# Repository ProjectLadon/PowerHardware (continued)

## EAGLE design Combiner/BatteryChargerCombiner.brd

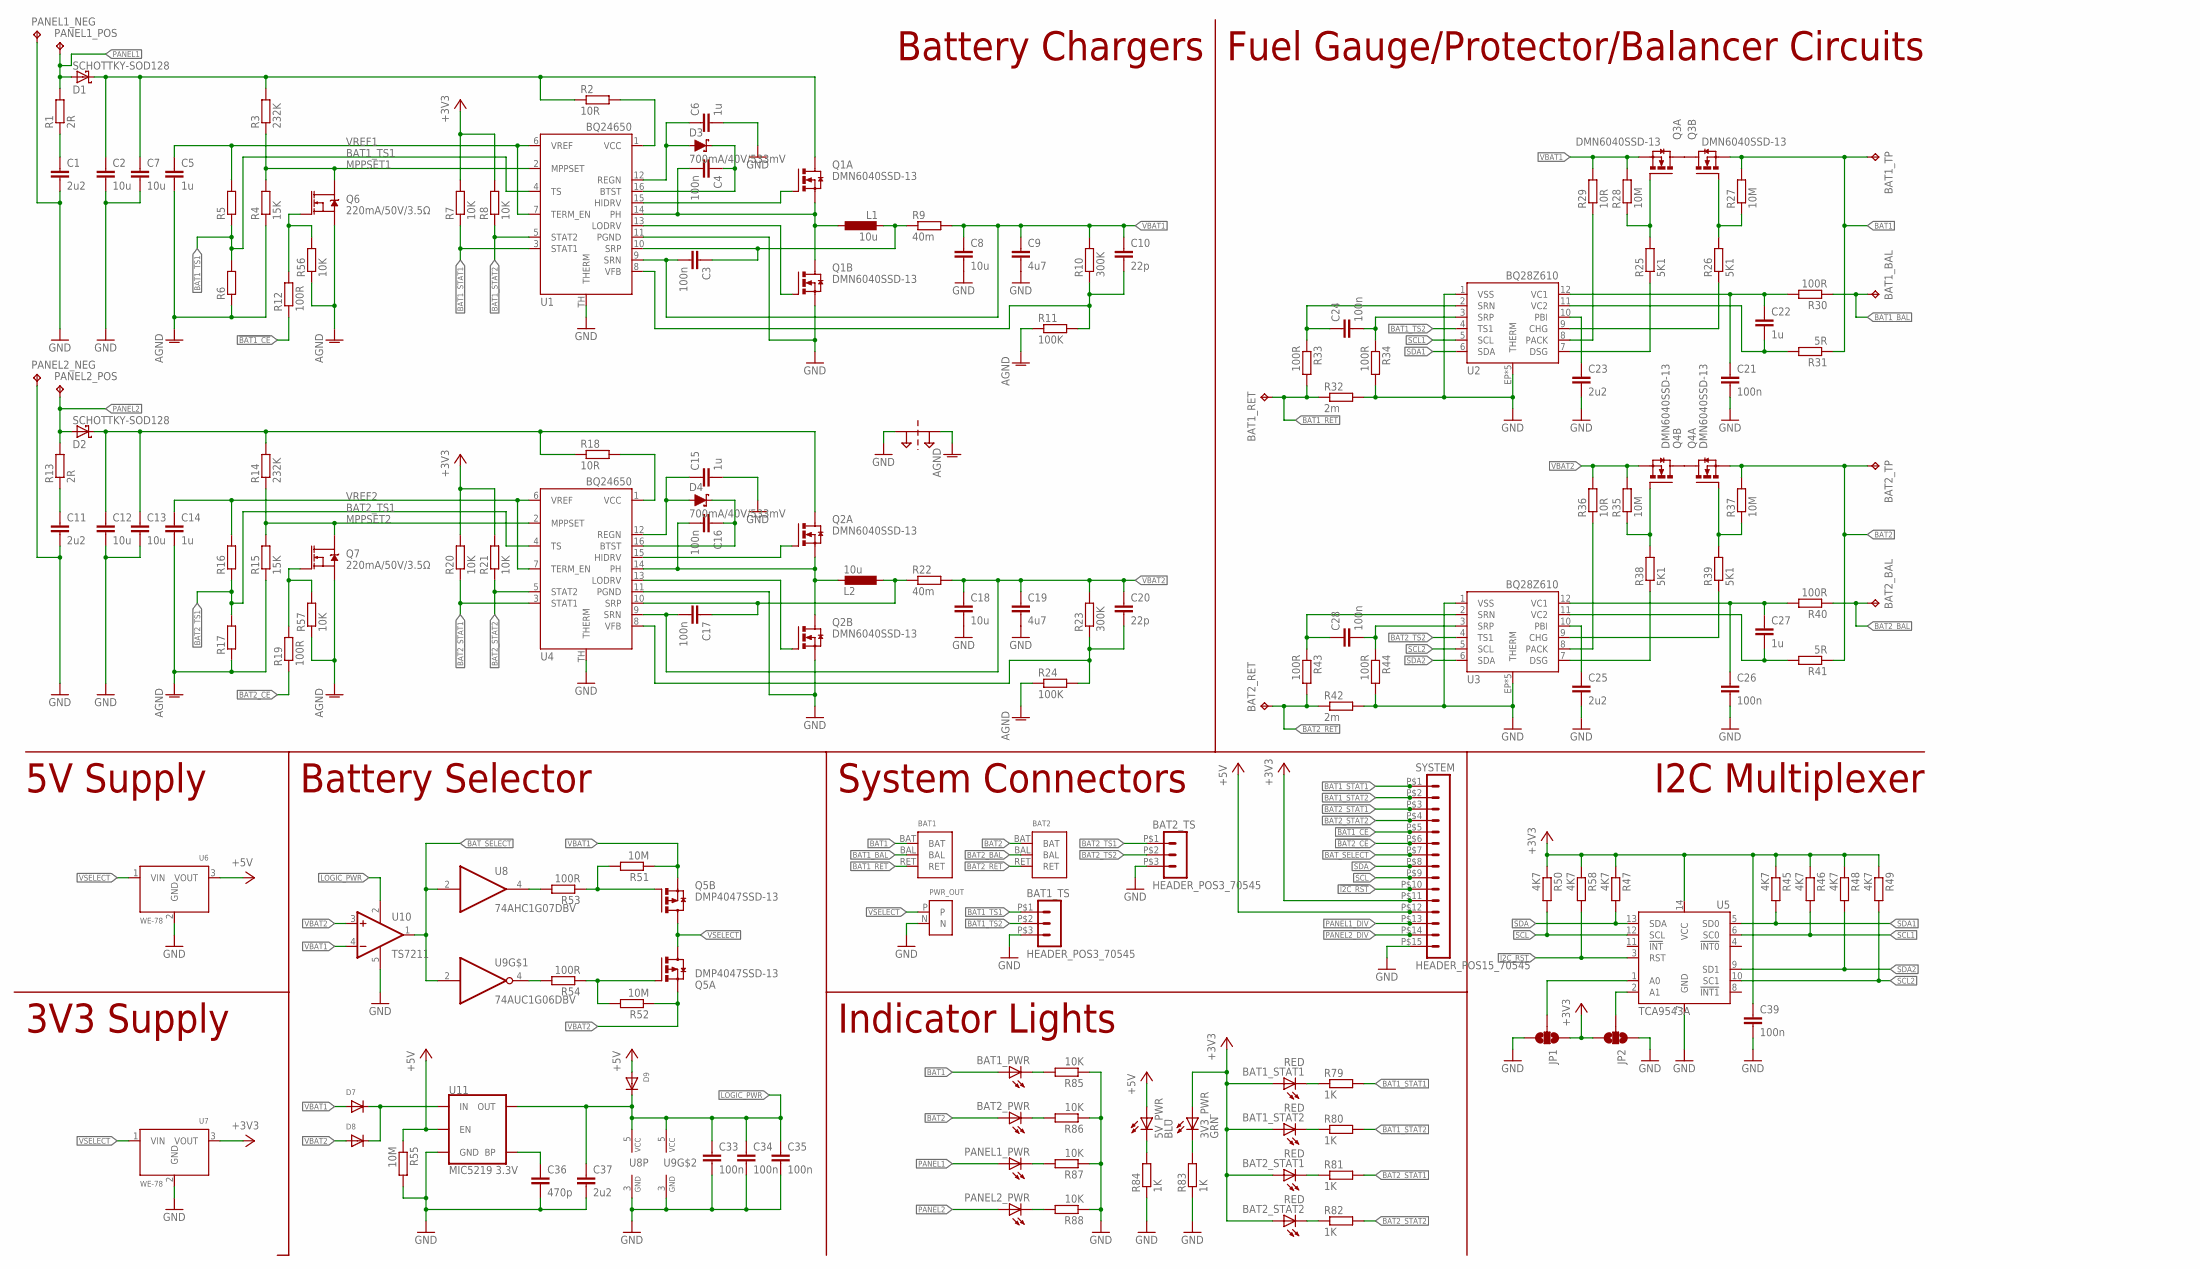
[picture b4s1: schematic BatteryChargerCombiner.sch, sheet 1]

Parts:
3V3_PWR: GRN; CHIP-LED0603
5V_PWR: BLU; CHIP-LED0603
BAT1, BAT2: 2S-BATTERYSMD; JST-XH3-SMD
BAT1_BAL, BAT1_RET, BAT1_TP, BAT2_BAL, BAT2_RET, BAT2_TP: TPPAD1-13Y; P1-13Y
BAT1_PWR, BAT2_PWR: LEDCHIP-LED0603; CHIP-LED0603
BAT1_STAT1, BAT1_STAT2, BAT2_STAT1, BAT2_STAT2: RED; CHIP-LED0603
BAT1_TS, BAT2_TS: HEADER_POS3_70545; 70545-POS3
C1, C11, C23, C25, C37: 2u2; C0603
C2, C7, C8, C12, C13, C18: 10u; C1210
C3, C4, C16, C17, C21, C24, C26, C28, C33, C34, C35, C39: 100n; C0603
C5, C6, C14, C15, C22, C27: 1u; C0603
C9, C19: 4u7; C1210
C10, C20: 22p; C0603
C36: 470p; C0603
D1, D2: SCHOTTKY-SOD128; SOD-128
D3, D4: 700mA/40V/533mV; SOT23-3
D7, D8, D9: DIODESOD-123; SOD-123
JP1, JP2: JUMPER-SMT_3_NO_SILK; SMT-JUMPER_3_NO_SILK
L1, L2: 10u; DG6050
PANEL1_NEG, PANEL1_POS, PANEL2_NEG, PANEL2_POS: TPPAD1-13Y; P1-13Y
PANEL1_PWR, PANEL2_PWR: LEDCHIP-LED0603; CHIP-LED0603
PWR_OUT: PWR; JST-XH2-THRUHOLE
Q1, Q2, Q3, Q4: DMN6040SSD-13; SO-08
Q5: DMP4047SSD-13; SO08
Q6, Q7: 220mA/50V/3.5Ω; SOT23-3
R1, R13: 2R; R0603
R2, R18: 10R; R1206
R3, R14: 232K; R0603
R4, R15: 15K; R0603
R5, R6, R16, R17: R-EU_R0603; R0603
R7, R8, R20, R21, R56, R57, R85, R86, R87, R88: 10K; R0603
R9, R22: 40m; R2512
R10, R23: 300K; R0603
R11, R24: 100K; R0603
R12, R19, R30, R33, R34, R40, R43, R44, R53, R54: 100R; R0603
R25, R26, R38, R39: 5K1; R0603
R27, R28, R35, R37, R51, R52, R55: 10M; R0603
R29, R36: 10R; R0603
R31, R41: 5R; R0603
R32, R42: 2m; R2512
R45, R46, R47, R48, R49, R50, R58: 4K7; R0603
R79, R80, R81, R82, R83, R84: 1K; R0603
SUPPLY1: 2PT_GND_TIE
SYSTEM: HEADER_POS15_70545; 70545-POS15
U1, U4: BQ24650; QFN16
U2, U3: BQ28Z610; PDSO-N12
U5: TCA9543A; SO-14
U6, U7: WE-78
U8: 74AHC1G07DBV; SOT23-5
U9: 74AUC1G06DBV; SOT23-5
U10: TS7211; DBV-R-PDSO-G5
U11: MIC5219 3.3V; SOT23-5

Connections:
!BAT1_CE!: R12.1, SYSTEM.P$5 (5); also elsewhere on the board
!BAT2_CE!: R19.1, SYSTEM.P$6 (6); also elsewhere on the board
!I2C_RST!: R58.2, SYSTEM.P$10 (10), U5.3 (RST); also elsewhere on the board
+3V3: 3V3_PWR.A, BAT1_STAT1.A, BAT1_STAT2.A, BAT2_STAT1.A, BAT2_STAT2.A, C39.1, JP1.1, JP2.3, R7.2, R8.2, R20.2, R21.2, R45.1, R46.1, R47.1, R48.1, R49.1, R50.1, R58.1, SYSTEM.P$11 (11), U5.14 (VCC), U7.3 (VOUT); also elsewhere on the board
+5V: 5V_PWR.A, D9.A, R55.1, SYSTEM.P$12 (12), U6.3 (VOUT), U11.3 (EN); also elsewhere on the board
AGND: C5.2, C14.2, Q6.2 (S), Q7.2 (S), R4.1, R6.1, R11.1, R15.1, R17.1, R24.1, R56.1, R57.1, SUPPLY1.P$2
BAT1: BAT1.BAT, BAT1_PWR.A, BAT1_TP.TP, Q3.1 (S), R27.2, R31.1
BAT1_BAL: BAT1.BAL, BAT1_BAL.TP, R30.1
BAT1_RET: BAT1.RET, BAT1_RET.TP, R32.1, R33.2
BAT1_STAT1: R7.1, R79.2, SYSTEM.P$1 (1), U1.3 (STAT1); also elsewhere on the board
BAT1_STAT2: R8.1, R80.2, SYSTEM.P$2 (2), U1.5 (STAT2); also elsewhere on the board
BAT1_TS1: BAT1_TS.P$1 (1), R5.1, R6.2, U1.4 (TS)
BAT1_TS2: BAT1_TS.P$2 (2), U2.4 (TS1)
BAT2: BAT2.BAT, BAT2_PWR.A, BAT2_TP.TP, Q4.3 (S), R37.2, R41.1
BAT2_BAL: BAT2.BAL, BAT2_BAL.TP, R40.1
BAT2_RET: BAT2.RET, BAT2_RET.TP, R42.1, R43.2
BAT2_STAT1: R20.1, R81.2, SYSTEM.P$3 (3), U4.3 (STAT1); also elsewhere on the board
BAT2_STAT2: R21.1, R82.2, SYSTEM.P$4 (4), U4.5 (STAT2); also elsewhere on the board
BAT2_TS1: BAT2_TS.P$1 (1), R16.1, R17.2, U4.4 (TS)
BAT2_TS2: BAT2_TS.P$2 (2), U3.4 (TS1)
BAT_SELECT: SYSTEM.P$7 (7), U8.2 (I), U9.2 (I), U10.1 (OUT); also elsewhere on the board
GND: BAT1_TS.P$3 (3), BAT2_TS.P$3 (3), C1.2, C2.2, C6.2, C7.2, C8.2, C9.2, C11.2, C12.2, C13.2, C15.2, C18.2, C19.2, C21.2, C23.2, C25.2, C26.2, C33.2, C34.2, C35.2, C36.2, C37.2, C39.2, JP1.3, JP2.1, PANEL1_NEG.TP, PANEL2_NEG.TP, PWR_OUT.N, Q1.1 (S), Q2.1 (S), R32.2, R34.2, R42.2, R44.2, R55.2, R83.1, R84.1, R85.1, R86.1, R87.1, R88.1, SUPPLY1.P$1, SYSTEM.P$15 (15), U1.11 (PGND), U1.TH (THERM), U2.1 (VSS), U2.EP (THERM), U2.EP1 (THERM), U2.EP2 (THERM), U2.EP3 (THERM), U2.EP4 (THERM), U3.1 (VSS), U3.EP (THERM), U3.EP1 (THERM), U3.EP2 (THERM), U3.EP3 (THERM), U3.EP4 (THERM), U4.11 (PGND), U4.TH (THERM), U5.7 (GND), U6.2 (GND), U7.2 (GND), U8.3 (GND), U9.3 (GND), U10.5 (GND), U11.2 (GND); also elsewhere on the board
LOGIC_PWR: C33.1, C34.1, C35.1, C37.1, D9.C, U8.5 (VCC), U9.5 (VCC), U10.2 (V+), U11.5 (OUT)
MPPSET1: Q6.3 (D), R3.1, R4.2, U1.2 (MPPSET)
MPPSET2: Q7.3 (D), R14.1, R15.2, U4.2 (MPPSET)
unnamed: C1.1, R1.1
unnamed: R2.2, U1.1 (VCC)
unnamed: C2.1, C7.1, D1.C, Q1.5 (D), Q1.6 (D), R2.1, R3.2
unnamed: Q1.4 (G), U1.15 (HIDRV)
unnamed: C4.2, L1.1, Q1.3 (S), Q1.7 (D), Q1.8 (D), U1.14 (PH)
unnamed: Q1.2 (G), U1.13 (LODRV)
unnamed: Q6.1 (G), R12.2, R56.2
unnamed: C3.1, L1.2, R9.1, U1.10 (SRP)
unnamed: C4.1, D3.3 (C), U1.16 (BTST)
unnamed: C6.1, D3.1 (A), U1.12 (REGN)
unnamed: C10.2, R10.1, R11.2, U1.8 (VFB)
unnamed: Q2.4 (G), U4.15 (HIDRV)
unnamed: BAT1_STAT1.C, R79.1
unnamed: C11.1, R13.1
unnamed: C15.1, D4.1 (A), U4.12 (REGN)
unnamed: C16.1, D4.3 (C), U4.16 (BTST)
unnamed: R29.1, U2.8 (PACK)
unnamed: C12.1, C13.1, D2.C, Q2.5 (D), Q2.6 (D), R14.2, R18.1
unnamed: C16.2, L2.2, Q2.3 (S), Q2.7 (D), Q2.8 (D), U4.14 (PH)
unnamed: Q2.2 (G), U4.13 (LODRV)
unnamed: C17.1, L2.1, R22.1, U4.10 (SRP)
unnamed: R18.2, U4.1 (VCC)
unnamed: Q7.1 (G), R19.2, R57.2
unnamed: Q3.5 (D), Q3.6 (D), Q3.7 (D), Q3.8 (D)
unnamed: Q3.4 (G), R25.2, R28.1
unnamed: C20.2, R23.1, R24.2, U4.8 (VFB)
unnamed: Q3.2 (G), R26.2, R27.1
unnamed: R25.1, U2.7 (DSG)
unnamed: Q4.5 (D), Q4.6 (D), Q4.7 (D), Q4.8 (D)
unnamed: R26.1, U2.9 (CHG)
unnamed: C21.1, C22.1, R30.2, U2.12 (VC1)
unnamed: C22.2, R31.2, U2.11 (VC2)
unnamed: C23.1, U2.10 (PBI)
unnamed: C27.2, R41.2, U3.11 (VC2)
unnamed: C28.1, R43.1, U3.2 (SRN)
unnamed: C24.1, R33.1, U2.2 (SRN)
unnamed: Q4.2 (G), R35.1, R38.2
unnamed: C24.2, R34.1, U2.3 (SRP)
unnamed: Q4.4 (G), R37.1, R39.2
unnamed: C26.1, C27.1, R40.2, U3.12 (VC1)
unnamed: R36.1, U3.8 (PACK)
unnamed: R38.1, U3.7 (DSG)
unnamed: R39.1, U3.9 (CHG)
unnamed: C25.1, U3.10 (PBI)
unnamed: C28.2, R44.1, U3.3 (SRP)
unnamed: BAT1_STAT2.C, R80.1
unnamed: Q5.4 (G), R51.2, R53.1
unnamed: BAT2_STAT1.C, R81.1
unnamed: JP1.2, U5.1 (A0)
unnamed: JP2.2, U5.2 (A1)
unnamed: Q5.2 (G), R52.2, R54.1
unnamed: R54.2, U9.4 (O)
unnamed: R53.2, U8.4 (O)
unnamed: BAT2_STAT2.C, R82.1
unnamed: D7.C, D8.C, U11.1 (IN)
unnamed: C36.1, U11.4 (BP)
unnamed: 3V3_PWR.C, R83.2
unnamed: 5V_PWR.C, R84.2
unnamed: BAT1_PWR.C, R85.2
unnamed: BAT2_PWR.C, R86.2
unnamed: PANEL1_PWR.C, R87.2
unnamed: PANEL2_PWR.C, R88.2
PANEL1: D1.A, PANEL1_POS.TP, PANEL1_PWR.A, R1.2; also elsewhere on the board
PANEL1_DIV: SYSTEM.P$13 (13); also elsewhere on the board
PANEL2: D2.A, PANEL2_POS.TP, PANEL2_PWR.A, R13.2; also elsewhere on the board
PANEL2_DIV: SYSTEM.P$14 (14); also elsewhere on the board
SCL: R50.2, SYSTEM.P$9 (9), U5.12 (SCL); also elsewhere on the board
SCL1: R46.2, U2.5 (SCL), U5.6 (SC0)
SCL2: R49.2, U3.5 (SCL), U5.10 (SC1)
SDA: R47.2, SYSTEM.P$8 (8), U5.13 (SDA); also elsewhere on the board
SDA1: R45.2, U2.6 (SDA), U5.5 (SD0)
SDA2: R48.2, U3.6 (SDA), U5.9 (SD1)
VBAT1: C3.2, C8.1, C9.1, C10.1, D7.A, Q3.3 (S), Q5.3 (S), R9.2, R10.2, R28.2, R29.2, R51.1, U1.9 (SRN), U10.4 (-IN)
VBAT2: C17.2, C18.1, C19.1, C20.1, D8.A, Q4.1 (S), Q5.1 (S), R22.2, R23.2, R35.2, R36.2, R52.1, U4.9 (SRN), U10.3 (+IN)
VREF1: C5.1, R5.2, U1.6 (VREF), U1.7 (TERM_EN)
VREF2: C14.1, R16.2, U4.6 (VREF), U4.7 (TERM_EN)
VSELECT: PWR_OUT.P, Q5.5 (D), Q5.6 (D), Q5.7 (D), Q5.8 (D), U6.1 (VIN), U7.1 (VIN); also elsewhere on the board

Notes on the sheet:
Battery Chargers
Fuel Gauge/Protector/Balancer Circuits
I2C Multiplexer
5V Supply
3V3 Supply
Battery Selector
System Connectors
Indicator Lights

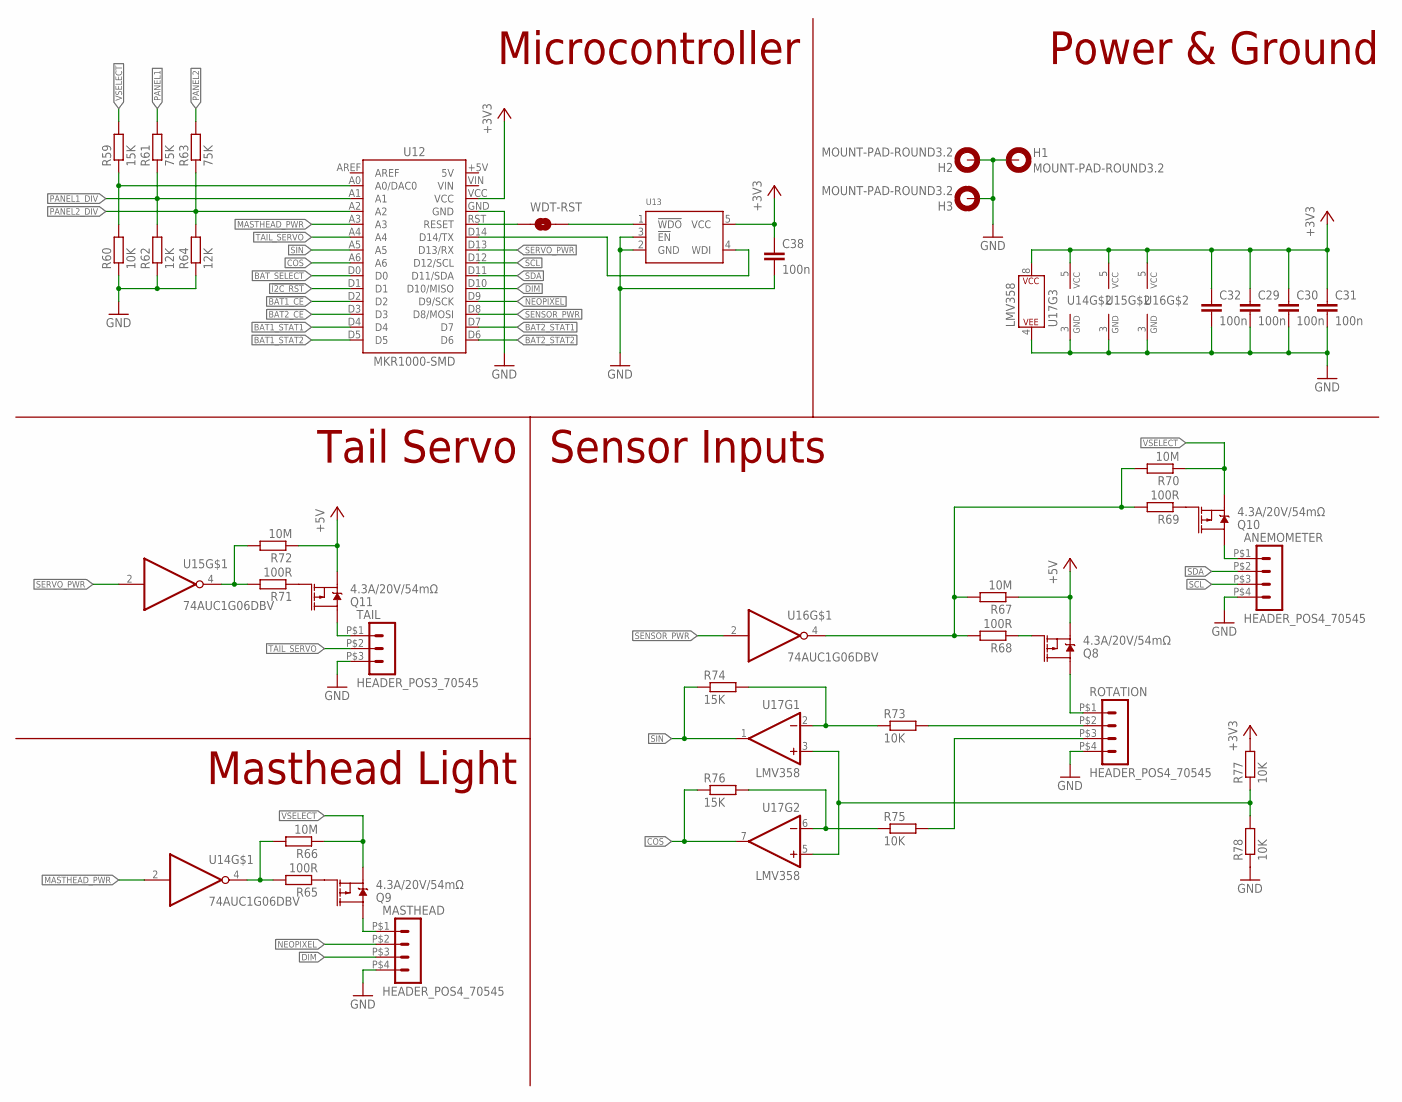
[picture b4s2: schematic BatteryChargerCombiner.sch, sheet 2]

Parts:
ANEMOMETER: HEADER_POS4_70545; 70545-POS4
C29, C30, C31, C32, C38: 100n; C0603
H1, H2, H3: MOUNT-PAD-ROUND3.2; 3,2-PAD
MASTHEAD: HEADER_POS4_70545; 70545-POS4
Q8, Q9, Q10, Q11: 4.3A/20V/54mΩ; SOT23-3
R59, R74, R76: 15K; R0603
R60, R73, R75, R77, R78: 10K; R0603
R61, R63: 75K; R0603
R62, R64: 12K; R0603
R65, R68, R69, R71: 100R; R0603
R66, R67, R70, R72: 10M; R0603
ROTATION: HEADER_POS4_70545; 70545-POS4
TAIL: HEADER_POS3_70545; 70545-POS3
U12: MKR1000-SMD
U13: STWD100; DBV-R-PDSO-G5
U14, U15, U16: 74AUC1G06DBV; SOT23-5
U17: LMV358; SO08
WDT-RST: JUMPER-SMT_2_NO_SILK; SMT-JUMPER_2_NO_SILK

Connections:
!BAT1_CE!: U12.D2; also elsewhere on the board
!BAT2_CE!: U12.D3; also elsewhere on the board
!I2C_RST!: U12.D1; also elsewhere on the board
+3V3: C29.1, C30.1, C31.1, C32.1, C38.1, R77.2, U12.VCC, U13.5 (VCC), U14.5 (VCC), U15.5 (VCC), U16.5 (VCC), U17.8 (P$V+); also elsewhere on the board
+5V: Q8.2 (S), Q11.2 (S), R67.1, R72.1; also elsewhere on the board
BAT1_STAT1: U12.D4; also elsewhere on the board
BAT1_STAT2: U12.D5; also elsewhere on the board
BAT2_STAT1: U12.D7; also elsewhere on the board
BAT2_STAT2: U12.D6; also elsewhere on the board
BAT_SELECT: U12.D0; also elsewhere on the board
COS: R76.1, U12.A6, U17.7 (OUT)
COS_IN: R75.2, ROTATION.P$3 (3)
DIM: MASTHEAD.P$3 (3), U12.D10 (D10/MISO)
GND: ANEMOMETER.P$4 (4), C29.2, C30.2, C31.2, C32.2, C38.2, H1.B3,2, H2.B3,2, H3.B3,2, MASTHEAD.P$4 (4), R60.1, R62.1, R64.1, R78.1, ROTATION.P$4 (4), TAIL.P$3 (3), U12.GND, U13.2 (GND), U13.3 (!EN!), U14.3 (GND), U15.3 (GND), U16.3 (GND), U17.4 (P$V-); also elsewhere on the board
MASTHEAD_PWR: U12.A3, U14.2 (I)
unnamed: Q8.3 (D), ROTATION.P$1 (1)
unnamed: Q8.1 (G), R68.1
unnamed: MASTHEAD.P$1 (1), Q9.3 (D)
unnamed: R59.1, R60.2, U12.A0 (A0/DAC0)
unnamed: U12.RST (RESET), WDT-RST.1
unnamed: R73.1, R74.2, U17.2 (-IN)
unnamed: Q9.1 (G), R65.1
unnamed: R65.2, R66.2, U14.4 (O)
unnamed: U13.1 (!WDO!), WDT-RST.2
unnamed: ANEMOMETER.P$1 (1), Q10.3 (D)
unnamed: Q10.1 (G), R69.1
unnamed: U12.D14 (D14/TX), U13.4 (WDI)
unnamed: R67.2, R68.2, R69.2, R70.2, U16.4 (O)
unnamed: Q11.3 (D), TAIL.P$1 (1)
unnamed: Q11.1 (G), R71.1
unnamed: R71.2, R72.2, U15.4 (O)
unnamed: R75.1, R76.2, U17.6 (-IN)
unnamed: R77.1, R78.2, U17.3 (+IN), U17.5 (+IN)
NEOPIXEL: MASTHEAD.P$2 (2), U12.D9 (D9/SCK)
PANEL1: R61.2; also elsewhere on the board
PANEL1_DIV: R61.1, R62.2, U12.A1; also elsewhere on the board
PANEL2: R63.2; also elsewhere on the board
PANEL2_DIV: R63.1, R64.2, U12.A2; also elsewhere on the board
SCL: ANEMOMETER.P$3 (3), U12.D12 (D12/SCL); also elsewhere on the board
SDA: ANEMOMETER.P$2 (2), U12.D11 (D11/SDA); also elsewhere on the board
SENSOR_PWR: U12.D8 (D8/MOSI), U16.2 (I)
SERVO_PWR: U12.D13 (D13/RX), U15.2 (I)
SIN: R74.1, U12.A5, U17.1 (OUT)
SIN_IN: R73.2, ROTATION.P$2 (2)
TAIL_SERVO: TAIL.P$2 (2), U12.A4
VSELECT: Q9.2 (S), Q10.2 (S), R59.2, R66.1, R70.1; also elsewhere on the board

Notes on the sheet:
Microcontroller
Sensor Inputs
Tail Servo
Masthead Light
Power & Ground

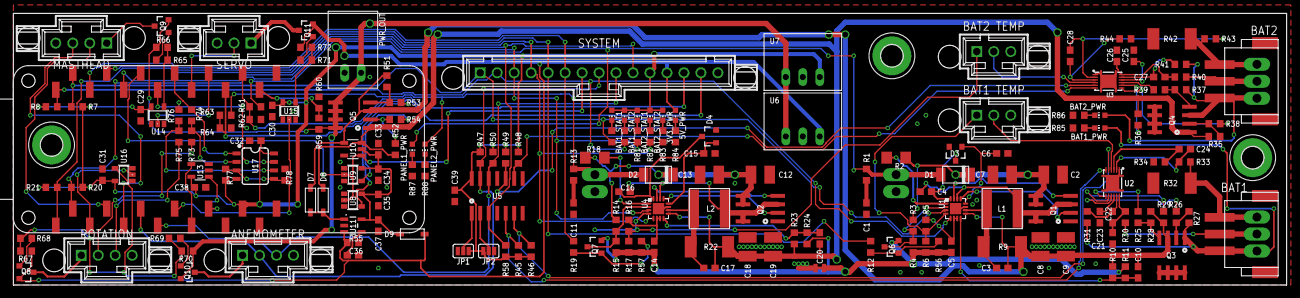
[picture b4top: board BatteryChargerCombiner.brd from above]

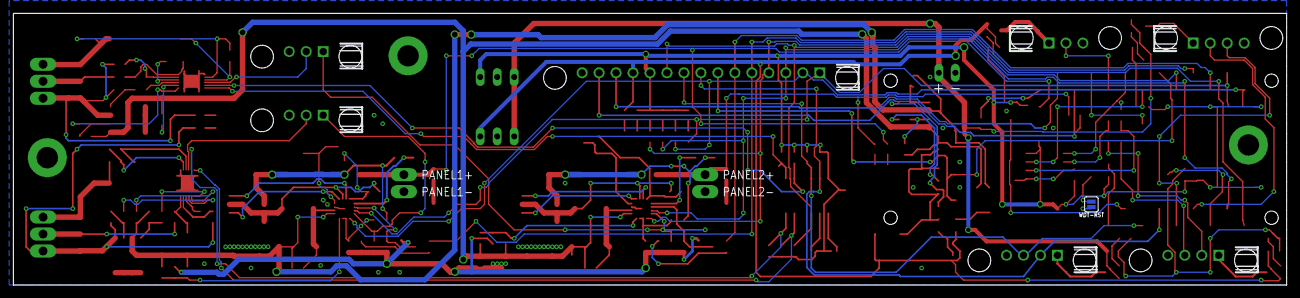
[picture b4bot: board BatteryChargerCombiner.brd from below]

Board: 2 copper layers, 190.5 x 40.6 mm, 201 parts (4 on the bottom side), 130 nets.

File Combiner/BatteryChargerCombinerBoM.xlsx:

Qty | Value | Device | Package | Parts | Description | Part Number | Manufacturer | Notes
3 |  | DIODESOD-123 | SOD-123 | D7, D8, D9 | Diode | MBR0580S1-7 | Diodes Inc | Digikey
2 |  | DIODESOT23_REFLOW | SOT23-R | D3, D4 | Diode | BAT750-TP | Micro Commercial | Digikey
4 |  | R-EU_R0603 | R0603 | R5, R6, R16, R17 | RESISTOR, European symbol |  |  | Digikey
2 | 100K | R-EU_R0603 | R0603 | R11, R24 | RESISTOR, European symbol | From stock |  | Digikey
14 | 100R | R-EU_R0603 | R0603 | R12, R19, R30, R33, R34, R40, R43, R44, R53, R54, R65, R68, R69, R71 | RESISTOR, European symbol | RC0603FR-07100RL | Yageo | Digikey
17 | 100n | C-EUC0603 | C0603 | C3, C4, C16, C17, C21, C24, C26, C28, C29, C30, C31, C32, C33, C34, C35, C38, C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 | CAPACITOR, European symbol | From stock |  | Digikey
15 | 10K | R-EU_R0603 | R0603 | R7, R8, R20, R21, R56, R57, R60, R73, R75, R77, R78, R85, R86, R87, R88 | RESISTOR, European symbol | From stock |  | Digikey
11 | 10M | R-EU_R0603 | R0603 | R27, R28, R35, R37, R51, R52, R55, R66, R67, R70, R72 | RESISTOR, European symbol | RC0603FR-0710ML | Yageo | Digikey
2 | 10R | R-EU_R0603 | R0603 | R29, R36 | RESISTOR, European symbol | RC0603FR-0710RL | Yageo | Digikey
2 | 10R | R-EU_R1206 | R1206 | R2, R18 | RESISTOR, European symbol | RC1206FR-0710RL | Yageo | Digikey
6 | 10u | C-EUC1210 | C1210 | C2, C7, C8, C12, C13, C18 | CAPACITOR, European symbol | CC1210ZKY5VGBB106 |  | Digikey
2 | 10u | INDUCTOR-DG6050 | DG6050 | L1, L2 |  | 1264EY-100M=P3 | Murata | Digikey
2 | 12K | R-EU_R0603 | R0603 | R62, R64 | RESISTOR, European symbol | From stock |  | Digikey
5 | 15K | R-EU_R0603 | R0603 | R4, R15, R59, R74, R76 | RESISTOR, European symbol | RC0603FR-0715KL | Yageo | Digikey
6 | 1K | R-EU_R0603 | R0603 | R79, R80, R81, R82, R83, R84 | RESISTOR, European symbol | From stock |  | Digikey
6 | 1u | C-EUC0603 | C0603 | C5, C6, C14, C15, C22, C27 | CAPACITOR, European symbol | From stock |  | Digikey
2 | 220mA/50V/3.5O | MOSFET-NCH-BSS138 | SOT23-3 | Q6, Q7 | N-channel MOSFETs | NTR5103NT1G | ON Semi | Digikey
2 | 22p | C-EUC0603 | C0603 | C10, C20 | CAPACITOR, European symbol | 06035A220JAT2A | AVX | Digikey
2 | 232K | R-EU_R0603 | R0603 | R3, R14 | RESISTOR, European symbol | RC0603FR-07232KL | Yageo | Digikey
2 | 2R | R-EU_R0603 | R0603 | R1, R13 | RESISTOR, European symbol | RMCF0603FT2R00 | Stackpole | Digikey
2 | 2S-BATTERYSMD | 2S-BATTERYSMD | JST-XH3-SMD | BAT1, BAT2 | JST XH connector for a 2S LiPo battery with balancing | S3B-XH-SM4-TB(LF)(SN) | JST | Digikey
2 | 2m | R-EU_R2512 | R2512 | R32, R42 | RESISTOR, European symbol | PA2512FKF070R002E | Yageo | Digikey
5 | 2u2 | C-EUC0603 | C0603 | C1, C11, C23, C25, C37 | CAPACITOR, European symbol | CL10A225KL8NNNC | Samsung | Digikey
2 | 300K | R-EU_R0603 | R0603 | R10, R23 | RESISTOR, European symbol | RC0603FR-07300KL | Yageo | Digikey
4 | 4.3A/20V/54mO | MOSFET_PCH-IRLML2244 | SOT23-3 | Q8, Q9, Q10, Q11 | P-channel MOSFETs | DMP3099L-7 | Diodes Inc | Digikey
2 | 40m | R-EU_R2512 | R2512 | R9, R22 | RESISTOR, European symbol | PE2512FKE070R04L | Yageo | Digikey
1 | 470p | C-EUC0603 | C0603 | C36 | CAPACITOR, European symbol | CL10B471KB8NNNC | Samsung | Digikey
7 | 4K7 | R-EU_R0603 | R0603 | R45, R46, R47, R48, R49, R50, R58 | RESISTOR, European symbol | From stock |  | Digikey
2 | 4u7 | C-EUC1210 | C1210 | C9, C19 | CAPACITOR, European symbol | CC1210KKX5R9BB475 |  | Digikey
4 | 5K1 | R-EU_R0603 | R0603 | R25, R26, R38, R39 | RESISTOR, European symbol | RC0603FR-075K1L | Yageo | Digikey
2 | 5R | R-EU_R0603 | R0603 | R31, R41 | RESISTOR, European symbol | RMCF0603FT4R99 | Stackpole | Digikey
1 | 74AHC1G07DBV | 74AHC1G07DBV | SOT23-5 | U8 | Single Buffer/Driver With Open-Drain Output | MC74VHC1G07DTT1G | ON Semi | Digikey
4 | 74AUC1G06DBV | 74AUC1G06DBV | SOT23-5 | U9, U14, U15, U16 | Single Inverter Buffer/Driver With Open-Drain Output | SN74LVC1G06DBVR | TI | Digikey
2 | 75K | R-EU_R0603 | R0603 | R61, R63 | RESISTOR, European symbol | RC0603FR-0775KL | Yageo | Digikey
5 | BLU | LEDCHIP-LED0603 | CHIP-LED0603 | 5V_PWR, BAT1_PWR, BAT2_PWR, PANEL1_PWR, PANEL2_PWR | LED | 150060BS75000 | Wurth | Digikey
2 | BQ24650 | BQ24650 | QFN16 | U1, U4 | TI LiPo charger with MPPT | BQ24650RVAT | TI | Digikey
2 | BQ28Z610 | BQ28Z610 | PDSO-N12 | U2, U3 | 2S LiPo balancer/fuel gauge | BQ28Z610DRZT | TI | Digikey
4 | DMN6040SSD-13 | IRF8313P | SO-08 | Q1, Q2, Q3, Q4 | HEXFET(R) Power MOSFET | DMN6040SSD-13 | Diodes Inc | Digikey
1 | DMP4047SSD-13 | DMP4047SSD-13 | SO08 | Q5 | Dual P MOSFET | DMP4047SSD-13 | Diodes Inc | Digikey
1 | GRN | LEDCHIP-LED0603 | CHIP-LED0603 | 3V3_PWR | LED | 150060GS75000 | Wurth | Digikey
1 | HEADER_POS15_70545 | HEADER_POS15_70545 | 70545-POS15 | SYSTEM | Molex -C-Gridï¿½ / SL Series connector | 705450049 | Molex | Digikey
3 | HEADER_POS3_70545 | HEADER_POS3_70545 | 70545-POS3 | BAT1_TS, BAT2_TS, TAIL | Molex -C-Gridï¿½ / SL Series connector | 705450072 | Molex | Digikey
3 | HEADER_POS4_70545 | HEADER_POS4_70545 | 70545-POS4 | ANEMOMETER, MASTHEAD, ROTATION | Molex -C-Gridï¿½ / SL Series connector | 705450003 | Molex | Digikey
1 | LMV358 | LMV358SOIC | SO08 | U17 | IC LMV358 DUAL OP AMP | LMV358SG-13 | Diodes Inc | Digikey
1 | MIC5219 3.3V | V_REG_MIC52193.3V | SOT23-5 | U11 | V_REG MIC5219 | MIC5219-3.3YM5-TR | Microchip | Digikey
1 | female Mill-Max 0.1" header strip | MKR1000-SMD | MKR1000-SMD | U12 | 0.1" SMD header -- cut to length. Mates with Mill-Max series 350 or 800 | ED4164-63-ND | Mill-Max | Digikey
1 | PWR | PWR | JST-XH2-THRUHOLE | PWR_OUT |  | S2B-XH-A(LF)(SN) | JST | Digikey
4 | RED | LEDCHIP-LED0603 | CHIP-LED0603 | BAT1_STAT1, BAT1_STAT2, BAT2_STAT1, BAT2_STAT2 | LED | 150060RS75000 | Wurth | Digikey
2 | SCHOTTKY-SOD128 | SCHOTTKY-SOD128 | SOD-128 | D1, D2 |  | PMEG4020ETP,115 | Nexperia | Digikey
1 | STWD100 | STWD100 | DBV-R-PDSO-G5 | U13 |  | STWD100NYWY3F | STM | Digikey
1 | TCA9543A | TCA9543A | SO-14 | U5 | 2 port I2C mux | TCA9543ADR | TI | Digikey
1 | TS7211 | TS7211 | DBV-R-PDSO-G5 | U10 | Single rail to rail differential comparator. | TS7211AILT | STM | Digikey
1 | WE-78 | 5V | WE-78 | U6 |  | 173950578 | Wurth | Digikey
1 | WE-78 | 3.3V | WE-78 | U7 |  | 173950378 | Wurth | Digikey

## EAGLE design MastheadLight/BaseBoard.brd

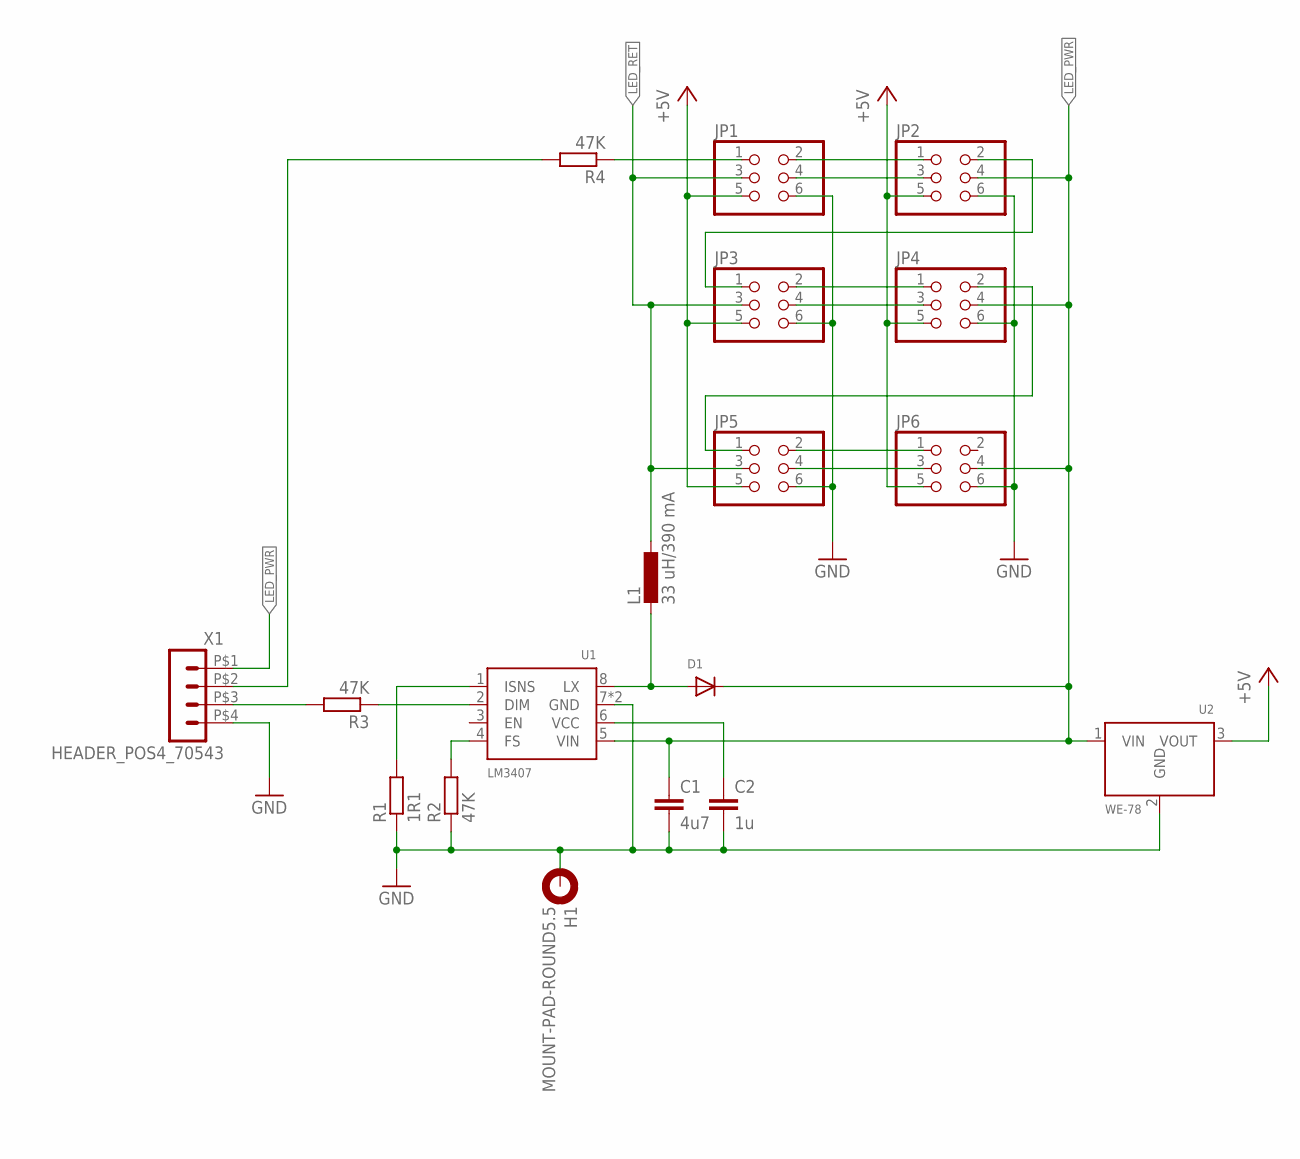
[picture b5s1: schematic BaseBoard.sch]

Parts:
C1: 4u7; C1206
C2: 1u; C0603
D1: DIODESOD-123; SOD-123
H1: MOUNT-PAD-ROUND5.5; 5,5-PAD
JP1, JP2, JP3, JP4, JP5, JP6: PINHD-2X3; 2X03
L1: 33 uH/390 mA; C1210
R1: 1R1; R1206
R2, R3, R4: 47K; R0603
U1: LM3407; MSOP8-GND
U2: WE-78
X1: HEADER_POS4_70543; 70543-POS4

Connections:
+5V: JP1.5, JP2.5, JP3.5, JP4.5, JP5.5, JP6.5, U2.3 (VOUT)
GND: C1.2, C2.2, H1.B5,5, JP1.6, JP2.6, JP3.6, JP4.6, JP5.6, JP6.6, R1.1, R2.1, U1.7 (GND), U1.THERM (GND), U2.2 (GND), X1.P$4 (4)
LED_PWR: C1.1, D1.C, JP2.4, JP4.4, JP6.4, U1.5 (VIN), U2.1 (VIN), X1.P$1 (1)
LED_RET: JP1.3, JP3.3, JP5.3, L1.1
unnamed: R1.2, U1.1 (ISNS)
unnamed: R2.2, U1.4 (FS)
unnamed: R3.1, U1.2 (DIM)
unnamed: D1.A, L1.2, U1.8 (LX)
unnamed: JP1.4, JP2.3
unnamed: C2.1, U1.6 (VCC)
unnamed: JP3.4, JP4.3
unnamed: JP5.4, JP6.3
unnamed: JP1.2, JP2.1
unnamed: JP2.2, JP3.1
unnamed: JP4.2, JP5.1
unnamed: JP5.2, JP6.1
unnamed: JP3.2, JP4.1
unnamed: R3.2, X1.P$3 (3)
unnamed: R4.2, X1.P$2 (2)
unnamed: JP1.1, R4.1

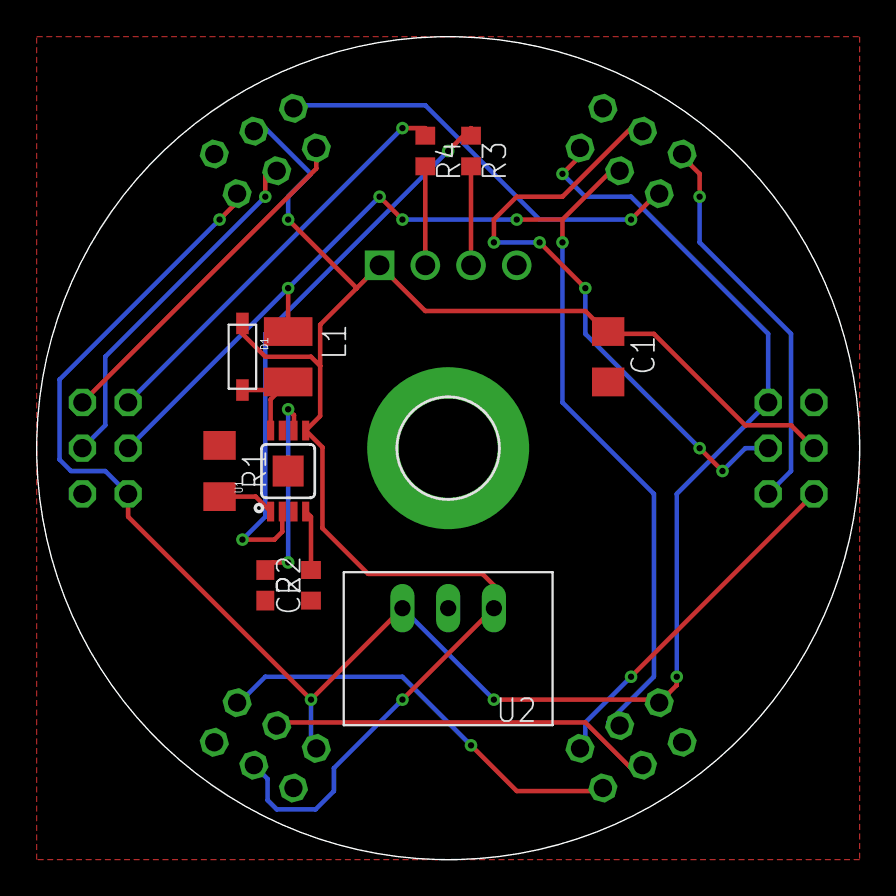
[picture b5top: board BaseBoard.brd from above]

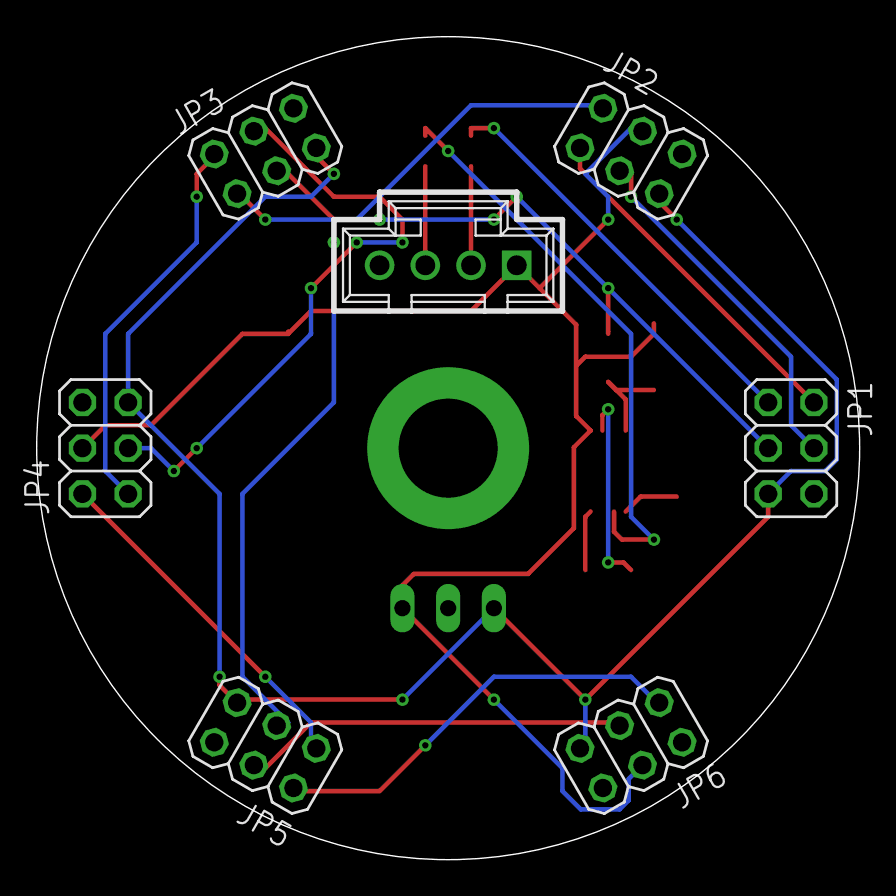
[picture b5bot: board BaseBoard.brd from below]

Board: 2 copper layers, 45.7 x 45.7 mm, 18 parts (7 on the bottom side), 20 nets.

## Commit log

2018-01-15 Creating charger/combiner board. Schematic complete, layout in progress
2018-01-15 All but four airwires routed
2018-01-15 All signals routed. TODO: Add connectors for all temp sensors and board resistors for protection circuit sensors. Add power switching & fuses for all outputs.
2018-01-16 Added temp sensor inputs, power switches, and mounting holes
2018-01-20 Silkscreen cleaned up; ready for test
2018-01-20 Now with selectable control schemes for the masthead light -- either I2C or PWM dimming & Neopixel
2018-01-20 Rationalized some traces
2018-01-21 Created masthead light boards
2018-01-22 Shrunk board width to 1600 mil, so it will fit inside a 1.5 in PVC pipe
2018-01-22 Now with idiot lights; still need to fix silkscreen around lights
2018-01-23 Put together BoM for battery charger/combiner. Left out everything except the trim resistors for the temp sensor'
2018-01-23 Put together BoM for the masthead light
2018-01-23 Switched the light board to the proper six-pin WS2812B footprint.
2018-01-24 As ordered state
2019-10-13 Committing the existing charger
2019-12-28 As per Dec 2019 board orders
2019-12-28 As per Dec 2019 board orders, part 2
